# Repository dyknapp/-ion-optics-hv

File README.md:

# Ion-optics HV supply - KiCad derivative

This is Daniel Knapp's configurable-polarity derivative of
[JQIamo/hv-piezo-driver](https://github.com/JQIamo/hv-piezo-driver), intended
for electrostatic ion-optics electrodes with a maximum output magnitude
of 250 V. Polarity is selected using zero-ohm links and a solder jumper
with power off and the output discharged.

- Open [the KiCad project](hardware/kicad/Eurocard-HV-piezo-driver.kicad_pro)
  using KiCad 10.0.7 or a compatible later version.
- Read the [project and configuration guide](hardware/kicad/README.md).
- Read the [dated changes and validation baseline](docs/MODIFICATIONS.md).

The original Eagle design, firmware, front-panel files and licence remain
in their original locations. The KiCad files in `hardware/kicad/` are the
editable source of the derivative. The inherited firmware has not yet been
adapted for this hardware's headless/I2C operation. This is an unvalidated
prototype baseline with documented outstanding rule-check findings.

## Provenance and documentation location

Initial derivative baseline: **2026-10-25**, on branch `ion-optics`, based on
upstream commit `8acd7d409c022f61565c32963c6fade5bf424614` (including the
PlatformIO update). The PCB is marked **PROTOTYPE - REV A**; that marking
does not identify a tested fabrication release.

Modified by Daniel Knapp with Codex assistance. Hardware documentation,
including the modified editable CAD, remains under [CERN OHL v1.2](LICENSE).
Retain upstream attribution and the separate firmware/library licence notices.

**Derivative public Documentation Location:**
[github.com/dyknapp/-ion-optics-hv](https://github.com/dyknapp/-ion-optics-hv).
The board's source link and QR code point to this repository. The original
upstream attribution and project notice are retained below.

**Signed: Codex (OpenAI), 2026-10-25.** This signature covers the derivative
notice above; the original project README below retains its upstream authorship.

---

# High voltage, low noise piezo driver

For more details, see our paper on the ArXiv: [[http://arxiv.org/abs/1609.03607]]

Release notes:

**v1.2**

* Teensy 32-bit ARM microcontroller used (MK20DX256VLH7)
* Voltage monitor now directly proportional to output voltage
* LP corner capacitor switch now properly biased at 2.5V (may have been true in v1.1 too).

**v1.2 errata**

* Voltage reading on MCU ADC not linear over full span; will require buffer after voltage divider.

Planned implementation in codebase:

* "unlimited digital integrator" -- uController integrates mod_in to zero with some given timeconstant. (DONE)
* scan module -- generate output scan/sweep. (easy to do, but need to find time. Stub `scan_module.h` file in code already)
* easier integration with eurocard backplane
* ... other?

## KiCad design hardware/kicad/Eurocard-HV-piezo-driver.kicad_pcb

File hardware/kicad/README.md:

# KiCad ion-optics prototype

Open `Eurocard-HV-piezo-driver.kicad_pro` with KiCad 10.0.7 or a compatible
later version. The project contains six schematic sheets and a four-layer
PCB. Its original filename is retained for schematic hierarchy and provenance.
This directory is the working source for the derivative; the Eagle files at
the repository root document the original design.

The project-local symbol library, `.pretty` footprint libraries, `sym-lib-table`
and `fp-lib-table` must travel with the CAD files. Both library tables use
`${KIPRJMOD}` paths. Install KiCad's standard symbol/footprint libraries as well;
several replacement footprints use them. No Eagle installation is required.

## Polarity configuration

The intended maximum output magnitude is 250 V. Change polarity only with
power off and the HV nodes discharged. Fit exactly one complete configuration:

| Output polarity | Fit zero-ohm links | Omit links | JP6 |
| --- | --- | --- | --- |
| Positive, default schematic population | R91, R92, R95 | R93, R94, R96 | Open |
| Negative | R93, R94, R96 | R91, R92, R95 | Bridged |

R91-R94 form the HV crossover. R95/R96 select the matching original/inverted
setpoint, and JP6 selects the monitor feedback configuration. Never fit both
sets: that can short the secondary path or connect the two setpoint outputs
together. For negative assembly, also change the fitted/DNP flags in the
schematic and any derived assembly BOM. The board has no relay-control or
automatic polarity-selection hardware.

The monitor reports positive magnitude for either correctly configured output
polarity. Its nominal gain differs between configurations, and it cannot
independently confirm the output sign. See [MODIFICATIONS.md](../../docs/MODIFICATIONS.md)
for the transfer equations and calibration caveats.

## Connections and selection headers

J1 is a DIN 41612 Type C connector with A/C rows populated. Its electrical
pinout is specific to this design; the Eurocard mechanics do not make it a
VME or other standard-bus module.

| J1 contacts | Signal |
| --- | --- |
| A1, C1 | GND |
| A30, C30 | -15 V |
| A31, C31 | +15 V |
| A25, C25 | HV_INTERLOCK |
| A14 | I2C_SDA |
| C14 | I2C_SCL |

The I2C connections are present in hardware. I2C peripheral/slave commands,
address selection, multi-board operation and headless control are not yet
implemented in the retained upstream firmware.

For J3 modulation-source selection, install either:

- Front BNC: shunts **3-4 and 5-6**.
- Backplane: shunts **1-3 and 5-7**.

The board diagrams show the top view. J3 pins 2 and 8 are unused. The front
modulation BNC has a differential signal return; do not assume its shield is
board ground.

J2/J4 patch rows 0-7 correspond to backplane channels, not MCU GPIO. In top
view, the four columns are GND, MOD, GPIO and OUT. MOD alternates positive
on rows 0/2/4/6 and negative on rows 1/3/5/7. OUT carries MON on rows 0-3
and AUX_DAC on rows 4-7. A same-row shunt from a J4 even pin to the adjacent
J2 odd pin selects a backplane modulation channel; a within-J2 shunt routes
MON/AUX to that backplane channel. A within-J4 shunt grounds the corresponding
modulation input.

J5 is the 2 mm MCU debug header. Pins 1-7 are 3V3, GND, TCK/SWCLK,
TDO/SWO, TDI, TMS/SWDIO and nRESET. The retained MK20 MCU needs the specified
PJRC-programmed bootloader device; a blank MKL02 is not an equivalent part.

## Editing, checks and fabrication records

Track the `.kicad_pro`, `.kicad_pcb`, `.kicad_dru`, all six `.kicad_sch`
files, local libraries and library tables. The repository ignores local UI
state, locks, caches, `.history/` and automatic backups. Curated BOM CSV/XML
files remain trackable. Optional `generated/`, `plots/` and `gerbers/`
directories here are ignored scratch locations; put deliberate release
packages in a separate versioned release directory.

Run ERC and PCB DRC, including zone refill and schematic parity, after changes.
The current baseline is not rule-clean; compare with the dated results in
[MODIFICATIONS.md](../../docs/MODIFICATIONS.md). The 1.25 mm HV rules are for
outer copper and specified net families, not a blanket clearance on every
layer or an independent creepage assessment. Review their exact net-name
lists after changing labels or reannotating the circuit.

Selected MPN, manufacturer and JLCPCB/LCSC fields are stored in the schematic.
C23's proposed replacement is explicitly a candidate rather than an approved
substitution. The sourcing work is a 2026-10-25 snapshot, not a stock guarantee.

Before a fabrication release, settle the remaining design/firmware decisions,
generate the matching BOM and manufacturing files, and tag that exact commit.
The inherited front-panel design still includes the original interface and
needs updating for the LCD-free instrument. The board's "PROTOTYPE - REV A"
marking is not evidence of bench validation.

## Board documentation link

The printed source link and QR1 both point to
[github.com/dyknapp/-ion-optics-hv](https://github.com/dyknapp/-ion-optics-hv).
QR1 is board-only artwork from `IonOptics.pretty/QR_Documentation.kicad_mod`,
excluded from the assembly BOM and placement files. It adds no pads or copper.

The QR code uses error correction Q, 33 x 33 modules at 0.45 mm pitch, and a
four-module quiet border: 18.45 mm square overall. Its centre is X151.225,
Y143.825 mm. Light silkscreen prints the background/quiet zone; darker solder
mask forms the code modules. Preserve the quiet zone and existing via tenting
beneath it. A solder-mask-subtracted silkscreen plot was decoded successfully
to the exact URL at three image resolutions before this commit.

Hardware documentation is licensed under [CERN OHL v1.2](../../LICENSE).
The derivative's public Documentation Location is the repository URL above.

**Signed: Codex (OpenAI), 2026-10-25.** Prepared for Daniel Knapp from the
reviewed schematic, PCB and modification records.

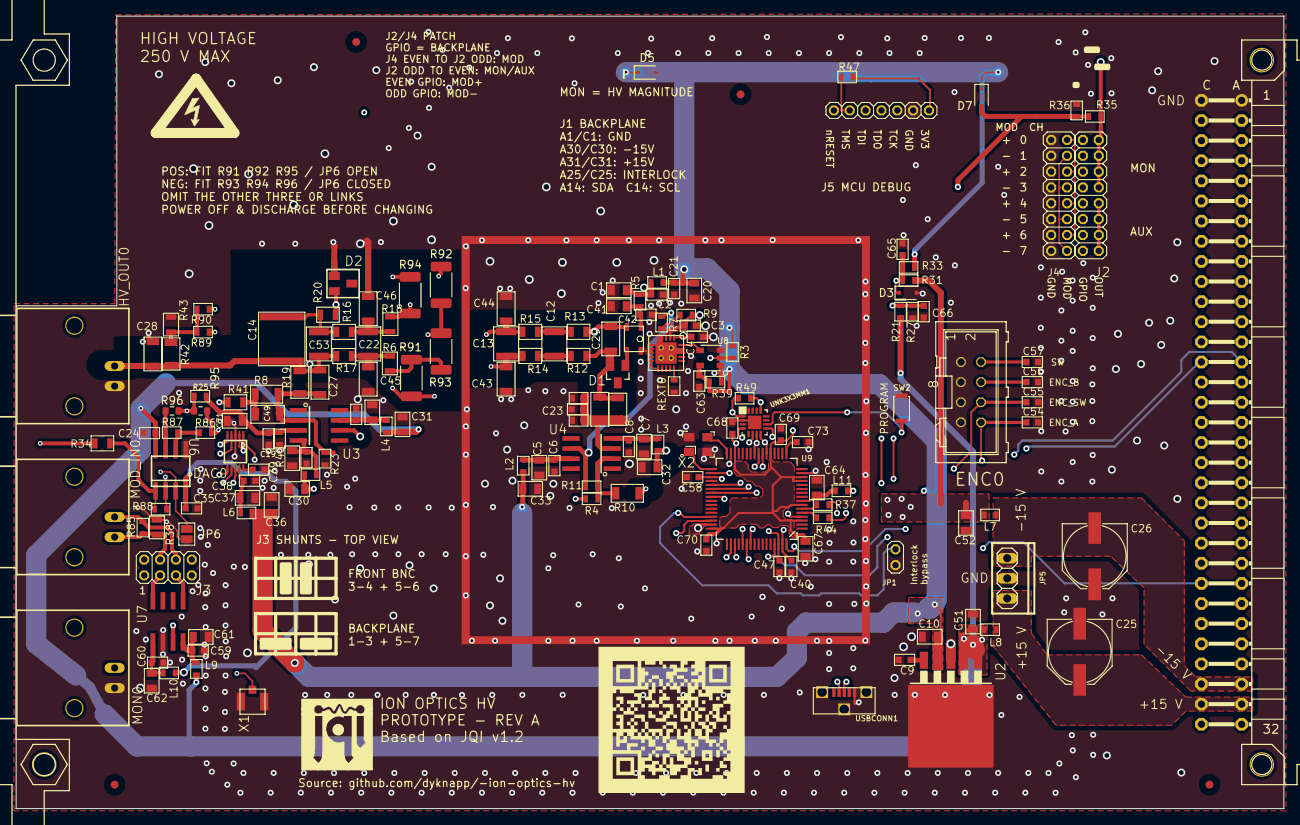
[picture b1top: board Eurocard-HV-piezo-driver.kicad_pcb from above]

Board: 4 copper layers, 160.0 x 100.0 mm, 172 parts (0 on the bottom side), 99 nets.

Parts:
C1, C5, C7, C10, C15, C17, C20, C30, C31, C32, C33, C36, C37, C41, C51, C52, C61, C62, C64, C67, C71: 10uF; C_MLCC_0805
C2, C3, C4, C6, C8, C16, C18, C21, C24, C35, C38, C39, C40, C42, C47, C54, C55, C56, C57, C58, C59, C60, C63, C65, C66, C68, C69, C70, C73: 100nF; C_MLCC_0603
C9: 470pF; C_MLCC_0603
C11: HV 22pF; C_MLCC_1206
C12, C13, C22, C53: HV 100nF; C_MLCC_1210
C14: HV 1uF; C_MLCC_2220
C19: 47nF; C_MLCC_0603
C23: 2.2nF; C_MLCC_0603
C25, C26: 220uF; PANASONIC_F
C27, C28, C29, C49: HV 1nF; C_MLCC_1206
C43, C44, C45, C46: HV 10nF; C_MLCC_1206
D1: DHVSD3004SSQ-7; SOT23
D2: AZ23C15-FDICT-ND; SOT-23
D3, D5, D7: Schottky; D_SOD-323F
DAC0: AD5663R; MSOP10
ENC0: PINHD-2X4-SHROUD; ML08
FID1, FID2, FID3, FID4: FIDUCIAL-1.0MM; FID_1.0MM
HV_OUT0: BNC-H; BNC90
J1: VG64C; VG64-CUTOUT
J2, J4: 2X8_LOW_PROFILE_JUMPER; 2X8_LOW_PROFILE_JUMPER_MATRIX
J3: 2X4_LOW_PROFILE_JUMPER; 2X4_LOW_PROFILE_JUMPER_MATRIX
J5: 1x7 2.00mm; 1X7_LOW_PROFILE
JP1: 1X2_LOW_PROFILE_JUMPER; 1X2_LOW_PROFILE
JP5: DNP; 1X03
JP6: MON_POL; SolderJumper-2_P1.3mm_Open_Pad1.0x1.5mm
L1, L2, L3, L4, L5, L6, L7, L8, L9, L10, L11: 1k @100MHz; L_FERRITE_0603
MOD_IN0: BNC-H; BNC90
MON0: BNC-H; BNC90
QR1: https://github.com/dyknapp/-ion-optics-hv; QR_Documentation
R3, R4, R7, R11, R27, R31, R35, R39, R47, R49, R85, R86, R87: 10k; R_0603
R5: 5.6R; R_0603
R6, R12, R13, R14, R15, R16, R17, R18: 499R; R_0805
R8, R19: 1M; R_1206
R9: 27.4k; R_0603
R10: 499k; R_1206
R20, R34, R38, R41: 49.9R; R_0805
R21: 200k; R_0603
R23, R25: 20.5k; R_0603
R33, R36: 3k; R_0603
R37, R44: 39R; R_0603
R42: 4.99M; R_1206
R43: 100k; R_0805
R45: 1M; R_0603
R88: 300k; R_0603
R89, R90: 100k; R_0603
R91, R92, R93, R94: 0R; R_2010_5025Metric
R95, R96: 0R; R_0603_1608Metric
REXT0: 10k; R_0603
RF_0A0, RF_0B0: 10k; R_0603
RF_SHIELD0: RF_36103505; 36103505-SHIELD
RI_0: 499k; R_1206
SW2: SWITCH-TACTILE; SWITCH-TACTILE-SMD
T1: ATB3225; ATB_TRANSFORMER
U1: DRV2700; S-PVQFN-N20
U2: MIC5209; TO263-5
U3, U4: LM7171; SO08$1
U6: OPA2172; SO08
U7: AD8421; SOIC-8
U8: 74AHCT1G02; SOT23-5
U9: MK20DX256VLH7; QFP50P1200X1200X160-64N
U$5: JQI_LOGO_NEGATIVE-SILKSCREEN@1
UNK3X3MM1: CURRENT_BOOTLOADER3X3MM; QFN50P300X300X100-17N
USBCONN1: MICRO-USB/1051330011; MICRO-USB_1051330011
X1: UMC
X2: 16MHz 7.2pF; CRYSTAL-3.2-2.5

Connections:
+5V: C10.P$1 (1), C20.P$1 (1), C21.P$1 (1), C33.P$1 (1), C36.P$1 (1), C63.P$1 (1), D5.1 (C), D7.1 (C), L1.P$1 (1), L2.P$1 (1), L6.P$2 (2), L11.P$2 (2), R3.P$2 (2), R33.P$2 (2), R39.P$1 (1), U2.4 (OUT), U8.P$5 (VCC)
+5V_UC: C64.P$2 (2), L11.P$1 (1), U9.8 (VREGIN)
+15V: C25.+, J1.A31, J1.C31, JP5.1, L8.P$1 (1)
-15V: C26.-, J1.A30, J1.C30, JP5.3, L7.P$1 (1)
/Eurocard-HV-piezo-driver_1/HV_FILTER_IN: R6.P$2 (2), R91.2, R93.2
/Eurocard-HV-piezo-driver_1/HV_PRE_FILTER_IN: C13.P$1 (1), C43.P$2 (2), R14.P$1 (1), R91.1, R94.1
/Eurocard-HV-piezo-driver_1/HV_PRE_RETURN_IN: C13.P$2 (2), C44.P$1 (1), R15.P$1 (1), R92.1, R93.1
/Eurocard-HV-piezo-driver_1/HV_RETURN_IN: R18.P$2 (2), R92.2, R94.2
/Eurocard-HV-piezo-driver_1/VDC_SET_INV: R87.P$1 (1), R96.1, U6.7 (OUT)
/Eurocard-HV-piezo-driver_1/VMON_NONINV: JP6.2 (B), R90.P$1 (1), U6.3 (+IN)
AUX_DAC: DAC0.2 (VOUTB), J2.P$10, J2.P$12, J2.P$14, J2.P$16, X1.P$1 (1)
BACKPLANE_MODIN_N: J3.P$1, J4.P$4, J4.P$8, J4.P$12, J4.P$16
BACKPLANE_MODIN_P: J3.P$7, J4.P$2, J4.P$6, J4.P$10, J4.P$14
DAC_CLR: DAC0.5 (CLR), U9.55 (D29/A18/SCL1)
DAC_CS: DAC0.6 (SYNC), U9.53 (D28/A17)
DAC_LDAC: DAC0.4 (LDAC), U9.54 (D27/A16)
D_N: R37.P$1 (1), USBCONN1.2 (D-)
D_P: R44.P$1 (1), USBCONN1.3 (D+)
EN: R3.P$1 (1), U8.P$2 (A), U9.46 (D9/RX2/PWM)
ENC_A: C54.P$1 (1), ENC0.8, U9.39 (D0/RX1/TOUCH)
ENC_B: C56.P$1 (1), ENC0.4, U9.64 (D5/PWM)
ENC_SW: C55.P$1 (1), ENC0.6, U9.40 (D1/TX1/TOUCH)
GND: C1.P$2 (2), C2.P$2 (2), C3.P$2 (2), C4.P$2 (2), C5.P$2 (2), C6.P$2 (2), C7.P$1 (1), C8.P$1 (1), C9.P$2 (2), C10.P$2 (2), C15.P$2 (2), C16.P$2 (2), C17.P$1 (1), C18.P$1 (1), C19.P$2 (2), C20.P$2 (2), C21.P$2 (2), C23.P$1 (1), C24.P$2 (2), C25.-, C26.+, C28.P$2 (2), C30.P$1 (1), C31.P$2 (2), C32.P$1 (1), C33.P$2 (2), C35.P$2 (2), C36.P$2 (2), C37.P$2 (2), C38.P$2 (2), C39.P$2 (2), C40.P$2 (2), C41.P$1 (1), C42.P$1 (1), C43.P$1 (1), C44.P$2 (2), C45.P$1 (1), C46.P$2 (2), C47.P$2 (2), C51.P$2 (2), C52.P$2 (2), C54.P$2 (2), C55.P$2 (2), C56.P$2 (2), C57.P$2 (2), C58.P$2 (2), C59.P$2 (2), C60.P$2 (2), C61.P$2 (2), C62.P$2 (2), C63.P$2 (2), C64.P$1 (1), C65.P$2 (2), C66.P$2 (2), C67.P$1 (1), C68.P$1 (1), C69.P$1 (1), C70.P$1 (1), C71.P$2 (2), C73.P$1 (1), D2.1, D3.2 (A), D5.2 (A), DAC0.3 (GND), ENC0.1, ENC0.3, ENC0.5, ENC0.7, HV_OUT0.2, J1.A1, J1.C1, J4.P$1, J4.P$3, J4.P$5, J4.P$7, J4.P$9, J4.P$11, J4.P$13, J4.P$15, J5.P$2 (2), JP1.2, JP5.2, JP6.1 (A), MON0.2, R23.P$1 (1), R27.P$1 (1), R36.P$1 (1), R38.P$1 (1), R43.P$1 (1), R45.P$1 (1), REXT0.P$1 (1), RF_0A0.P$2 (2), RF_0B0.P$2 (2), RF_SHIELD0.P$1 (GND), RF_SHIELD0.P$2 (GND), RF_SHIELD0.P$3 (GND), RF_SHIELD0.P$4 (GND), SW2.1, U1.4 (GND), U1.5 (GND), U1.6 (GND), U1.18 (GAIN0), U1.19 (GAIN1), U1.PAD (GND), U1.V1 (GND), U1.V2 (GND), U1.V3 (GND), U1.V4 (GND), U2.3 (GND), U2.6 (GND), U6.5 (+IN), U7.6 (REF), U8.P$3 (GND), U9.4 (VSS), U9.15 (VREF-L), U9.31 (VSS), U9.47 (VSS), UNK3X3MM1.2 (GND), UNK3X3MM1.17 (GND), USBCONN1.5 (GND), USBCONN1.P$1 (GND), USBCONN1.P$2 (GND), USBCONN1.P$3 (GND), X1.P$2 (2), X1.P$3 (2), X2.2 (GND), X2.4 (GND)
GND_0: C29.P$2 (2), R10.P$1 (1), R13.P$2 (2), T1.1
GPIO_0: J1.A3, J2.P$1
GPIO_1: J1.C3, J2.P$3
GPIO_2: J1.A4, J2.P$5
GPIO_3: J1.C4, J2.P$7
GPIO_4: J1.A6, J2.P$9
GPIO_5: J1.C6, J2.P$11
GPIO_6: J1.A7, J2.P$13
GPIO_7: J1.C7, J2.P$15
HV: C14.P$1 (1), C27.P$2 (2), C28.P$1 (1), C53.P$1 (1), HV_OUT0.1, R17.P$1 (1), R19.P$2 (2), R42.P$2 (2)
HV_0: C11.P$2 (2), C29.P$1 (1), D1.2 (C), R12.P$2 (2), RI_0.P$1 (1)
HV_INTERLOCK: J1.A25, J1.C25, JP1.1, R39.P$2 (2), U8.P$1 (B), U9.45 (D23/A9/PWM/TOUCH)
HV_MIDGND: C14.P$2 (2), C53.P$2 (2), R16.P$1 (1), R20.P$1 (1)
I2C_SCL: J1.C14, U9.37 (D19/A5/SCL0/TOUCH)
I2C_SDA: J1.A14, U9.38 (D18/A4/SDA0/TOUCH)
JTAG_TCLK/SWD_KLK/EZP_CLK: J5.P$3 (3), U9.22 (PTA0), UNK3X3MM1.8 (PTB0)
JTAG_TDI/EZP_DI: J5.P$5 (5), U9.23 (PTA1), UNK3X3MM1.6 (PTA6)
JTAG_TDO/TRACE_SWO/EZP_DO: J5.P$4 (4), U9.24 (PTA2), UNK3X3MM1.9 (PTB1)
JTAG_TMS/SWD_DIO: J5.P$6 (6), R47.P$2 (2), U9.25 (PTA3), UNK3X3MM1.7 (PTA7)
MOSI: DAC0.8 (DATA), U9.51 (D11/MOSI)
unnamed: C4.P$1 (1), U1.1 (PUMP)
unnamed: C5.P$1 (1), C6.P$1 (1), L2.P$2 (2), U4.7 (V+)
unnamed: C7.P$2 (2), C8.P$2 (2), L3.P$2 (2), U4.4 (V-)
unnamed: C9.P$1 (1), U2.5 (FB)
unnamed: C11.P$1 (1), C23.P$2 (2), RF_0A0.P$1 (1), RF_0B0.P$1 (1), RI_0.P$2 (2), U4.3 (+IN)
unnamed: C12.P$1 (1), R12.P$1 (1), R14.P$2 (2)
unnamed: C12.P$2 (2), R13.P$1 (1), R15.P$2 (2)
unnamed: C15.P$1 (1), C16.P$1 (1), L4.P$2 (2), U3.7 (V+)
unnamed: C17.P$2 (2), C18.P$2 (2), L5.P$2 (2), U3.4 (V-)
unnamed: C22.P$1 (1), C45.P$2 (2), R6.P$1 (1), R17.P$2 (2)
unnamed: C22.P$2 (2), C46.P$1 (1), R16.P$2 (2), R18.P$1 (1)
unnamed: C27.P$1 (1), C49.P$2 (2), R8.P$2 (2), R19.P$1 (1), R23.P$2 (2), U3.2 (-IN)
unnamed: C37.P$1 (1), C38.P$1 (1), DAC0.9 (VDD), L6.P$1 (1)
unnamed: C39.P$1 (1), DAC0.10 (VREF)
unnamed: C41.P$2 (2), C42.P$2 (2), R5.P$1 (1), T1.2
unnamed: C49.P$1 (1), R8.P$1 (1), R41.P$2 (2)
unnamed: C59.P$1 (1), C61.P$1 (1), L9.P$1 (1), U7.8 (+VS)
unnamed: C60.P$1 (1), C62.P$1 (1), L10.P$1 (1), U7.5 (-VS)
unnamed: C73.P$2 (2), U9.17 (VREF_OUT)
unnamed: D1.1 (A), T1.4
unnamed: D2.2, R20.P$2 (2), U3.6 (OUT)
unnamed: R4.P$1 (1), R10.P$2 (2), R11.P$1 (1), U4.2 (-IN)
unnamed: R7.P$2 (2), R11.P$2 (2), U4.6 (OUT)
unnamed: R34.P$1 (1), R88.P$1 (1), U6.1 (OUT)
unnamed: J3.P$4, MOD_IN0.2, R38.P$2 (2), R85.P$1 (1)
unnamed: R41.P$1 (1), U7.7 (VOUT)
unnamed: J3.P$6, MOD_IN0.1, R85.P$2 (2)
unnamed: R86.P$1 (1), R87.P$2 (2), U6.6 (-IN)
unnamed: R88.P$2 (2), R89.P$1 (1), U6.2 (-IN)
unnamed: T1.3, U1.7 (SW), U1.8 (SW)
unnamed: U1.10 (BST), U1.11 (BST)
unnamed: U1.20 (EN), U8.P$4 (Y)
unnamed: J3.P$3, U7.4 (IN+)
unnamed: J3.P$5, U7.1 (IN-)
unnamed: U9.32 (OSC1), X2.3 (C2)
unnamed: U9.33 (OSC2), X2.1 (C1)
PROGRAM_PUSHBUTTON: SW2.2, UNK3X3MM1.10 (PTB2)
REXT+: REXT0.P$2 (2), U1.15 (REXT)
SCK: DAC0.7 (CLK), U9.50 (D13/SCK/LED)
SW: C57.P$1 (1), ENC0.2, U9.61 (D6/PWM)
TEENSY_RESET: J5.P$7 (7), R49.P$2 (2), U9.34 (RESET), UNK3X3MM1.4 (PTA4), UNK3X3MM1.13 (PTB5)
TEENSY_VCC: C67.P$2 (2), C68.P$2 (2), C69.P$2 (2), C70.P$2 (2), J5.P$1 (1), R47.P$1 (1), R49.P$1 (1), U9.3 (VCC), U9.7 (VOUT3V3), U9.13 (VCCA), U9.14 (VREF-H), U9.21 (VBAT), U9.30 (VCC), U9.48 (VCC), UNK3X3MM1.1 (VDD)
USB_N: R37.P$2 (2), U9.6 (USB-M)
USB_P: R44.P$2 (2), U9.5 (USB-P)
V+: C24.P$1 (1), C31.P$1 (1), C51.P$1 (1), L4.P$1 (1), L8.P$2 (2), L9.P$2 (2), R21.P$2 (2), U2.1 (EN), U2.2 (IN), U6.8 (V+)
V+MON: C40.P$1 (1), C66.P$1 (1), R21.P$1 (1), R27.P$2 (2), U9.63 (D21/A7/PWM)
V-: C30.P$2 (2), C32.P$2 (2), C35.P$1 (1), C52.P$1 (1), L3.P$1 (1), L5.P$1 (1), L7.P$2 (2), L10.P$2 (2), R31.P$1 (1), U6.4 (V-)
V-MON: C47.P$1 (1), C65.P$1 (1), D3.1 (C), R31.P$2 (2), R33.P$1 (1), U9.62 (D20/A6/PWM)
VDC_FILT: C19.P$1 (1), C71.P$1 (1), R25.P$1 (1), R45.P$2 (2), U3.3 (+IN)
VDC_SET: DAC0.1 (VOUTA), R4.P$2 (2), R86.P$2 (2), R95.1
VDC_SET_POL_SLCTD: R25.P$2 (2), R95.2, R96.2
VDD_CONVERTER: C1.P$1 (1), C2.P$1 (1), C3.P$1 (1), L1.P$2 (2), R5.P$2 (2), R9.P$1 (1), U1.2 (VDD)
VMON: R42.P$1 (1), R43.P$2 (2), R89.P$2 (2), R90.P$2 (2)
VMON_BUF: J2.P$2, J2.P$4, J2.P$6, J2.P$8, MON0.1, R34.P$2 (2), R35.P$2 (2)
VMON_MON: C58.P$1 (1), D7.2 (A), R35.P$1 (1), R36.P$2 (2), U9.35 (D16/A2/TOUCH)
V_FB: R7.P$1 (1), R9.P$2 (2), U1.3 (FB)
